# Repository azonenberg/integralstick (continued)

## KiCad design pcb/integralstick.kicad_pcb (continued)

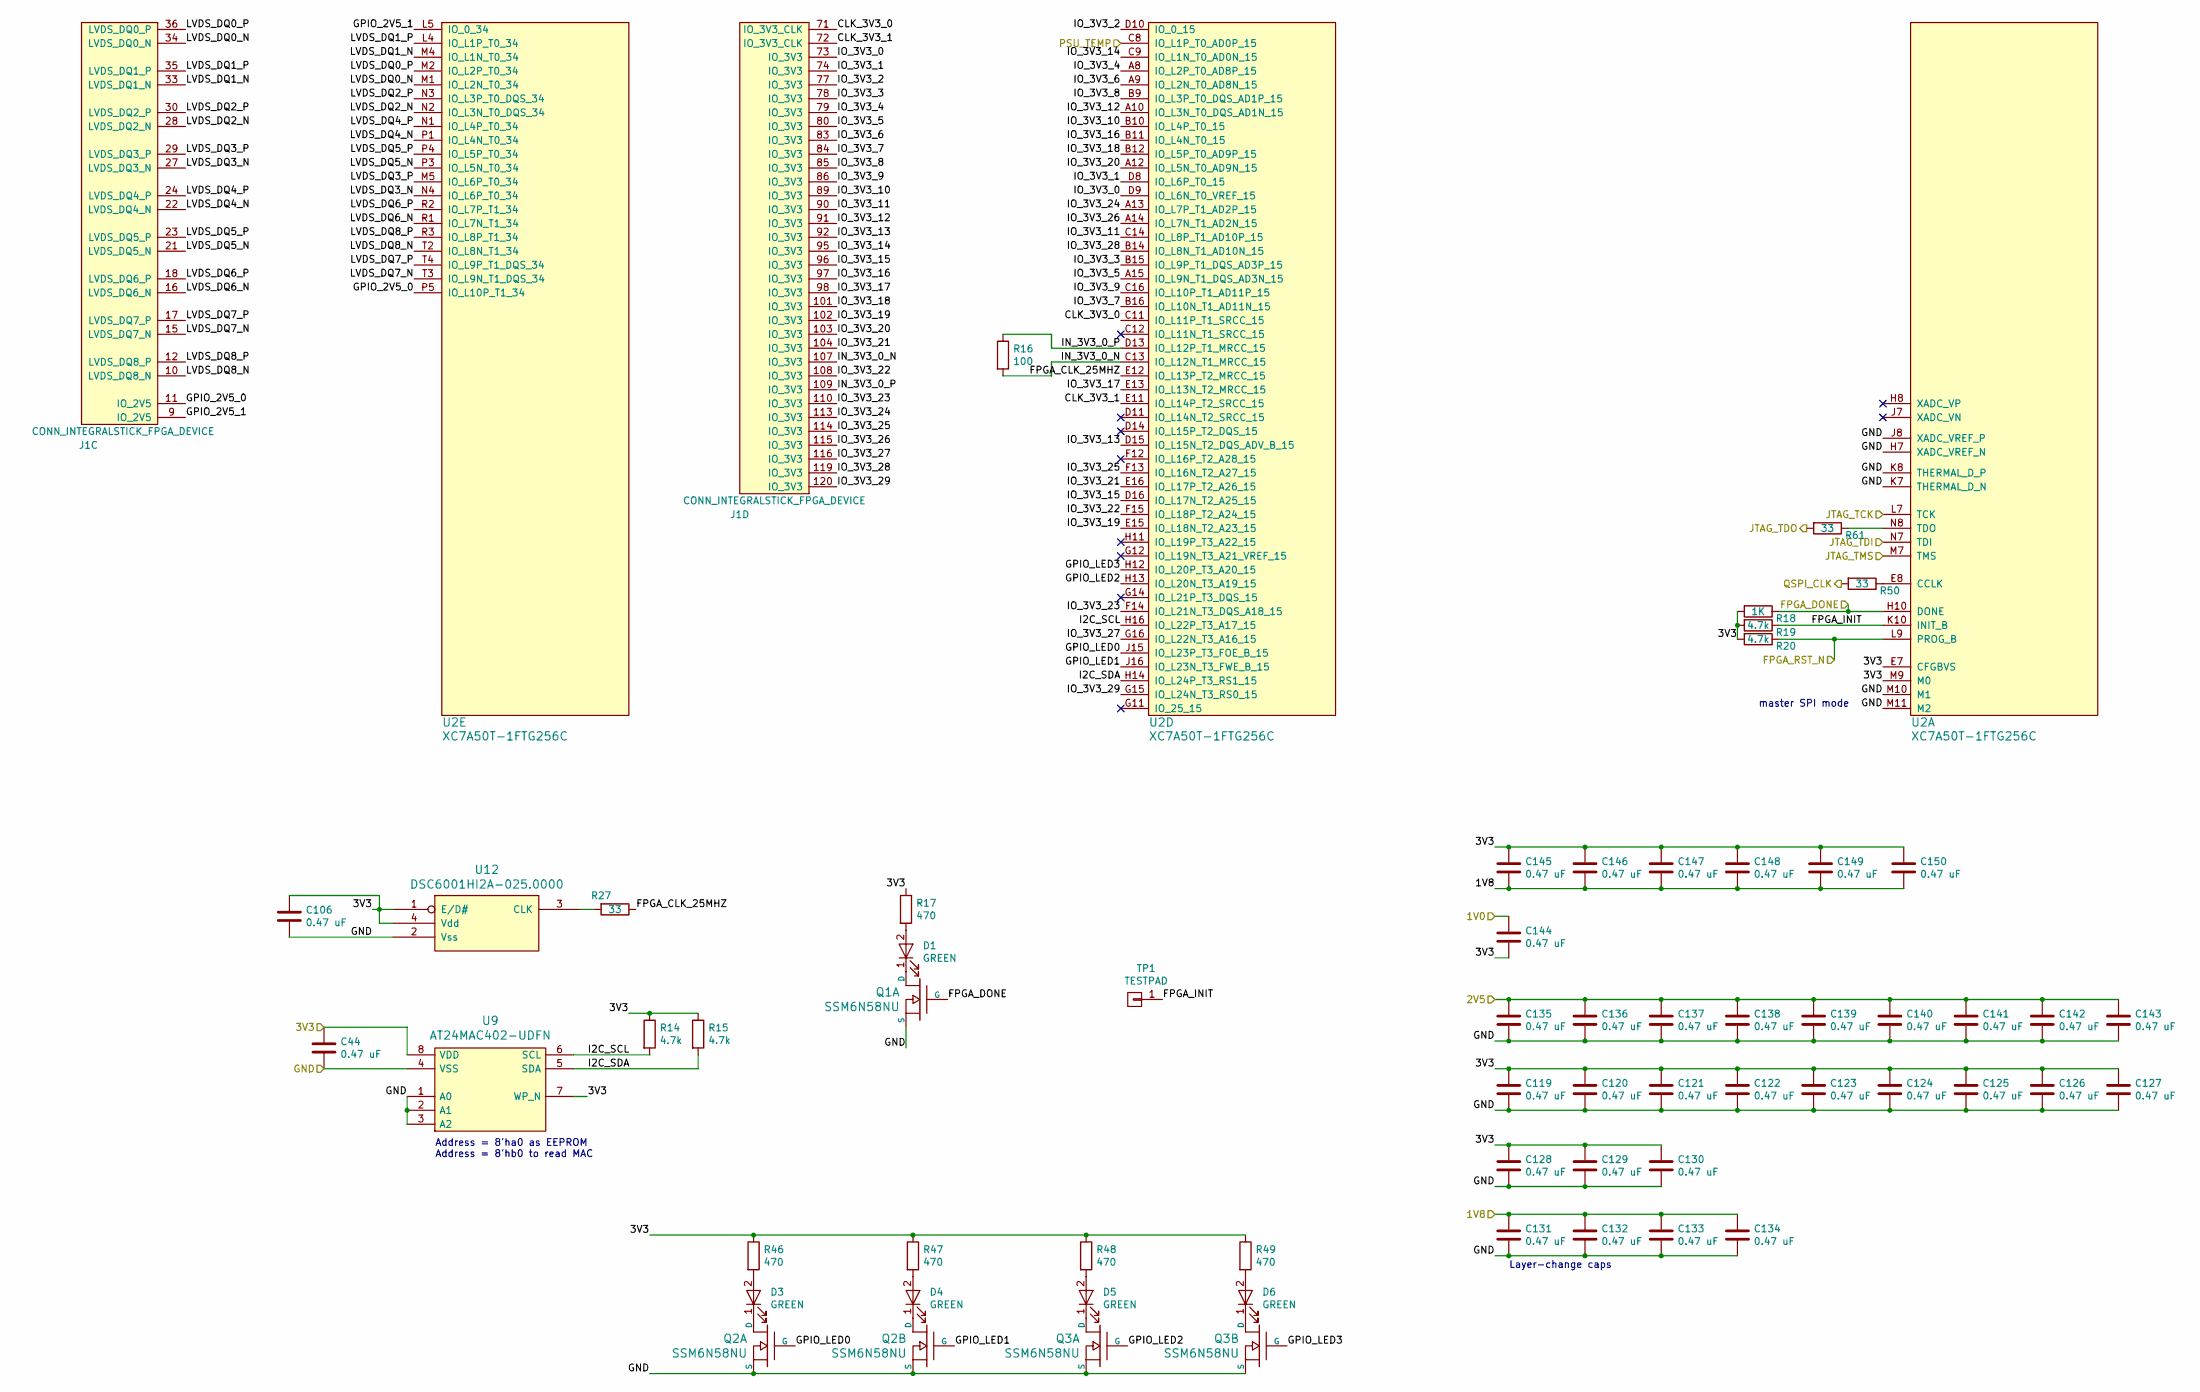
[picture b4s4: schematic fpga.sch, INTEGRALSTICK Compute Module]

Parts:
C44, C106, C119, C120, C121, C122, C123, C124, C125, C126, C127, C128, C129, C130, C131, C132, C133, C134, C135, C136, C137, C138, C139, C140, C141, C142, C143, C144, C145, C146, C147, C148, C149, C150: 0.47 uF; EIA_0402_CAP_NOSILK
D1, D3, D4, D5, D6: GREEN; EIA_0603_LED
J1: CONN_INTEGRALSTICK_FPGA_DEVICE; CONN_SAMTEC_QTH-060-01-L-D-A
Q1, Q2, Q3: SSM6N58NU; DFN_6_0.65MM_2x2MM_GDS
R14, R15, R19, R20: 4.7k; EIA_0402_RES_NOSILK
R16: 100; EIA_0402_RES_NOSILK
R17, R46, R47, R48, R49: 470; EIA_0402_RES_NOSILK
R18: 1K; EIA_0402_RES_NOSILK
R27, R50, R61: 33; EIA_0402_RES_NOSILK
TP1: TESTPAD; TESTPOINT_SMT_0.5MM
U2: XC7A50T-1FTG256C; BGA_256_17x17_FULLARRAY_1MM_0.4MM_FTG256
U9: AT24MAC402-UDFN; DFN_8_0.5MM_2x3MM
U12: DSC6001HI2A-025.0000‎; OSCILLATOR_1.6x1.2

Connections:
/1V0: C144.1; also elsewhere on the board
/1V8: C131.1, C132.1, C133.1, C134.1, C145.2, C146.2, C147.2, C148.2, C149.2, C150.2; also elsewhere on the board
/2V5: C135.1, C136.1, C137.1, C138.1, C139.1, C140.1, C141.1, C142.1, C143.1; also elsewhere on the board
/3V3: C44.1, C106.1, C119.1, C120.1, C121.1, C122.1, C123.1, C124.1, C125.1, C126.1, C127.1, C128.1, C129.1, C130.1, C144.2, C145.1, C146.1, C147.1, C148.1, C149.1, C150.1, R14.1, R15.1, R17.1, R18.2, R19.2, R20.2, R46.1, R47.1, R48.1, R49.1, U2.E7 (CFGBVS), U2.M9 (M0), U9.7 (WP_N), U9.8 (VDD), U12.1 (E/D#), U12.4 (Vdd); also elsewhere on the board
/FPGA/CLK_3V3_0: J1.71 (IO_3V3_CLK), U2.C11 (IO_L11P_T1_SRCC_15)
/FPGA/CLK_3V3_1: J1.72 (IO_3V3_CLK), U2.E11 (IO_L14P_T2_SRCC_15)
/FPGA/FPGA_CLK_25MHZ: R27.1, U2.E12 (IO_L13P_T2_MRCC_15)
/FPGA/FPGA_INIT: R19.1, TP1.1, U2.K10 (INIT_B)
/FPGA/GPIO_2V5_0: J1.11 (IO_2V5), U2.P5 (IO_L10P_T1_34)
/FPGA/GPIO_2V5_1: J1.9 (IO_2V5), U2.L5 (IO_0_34)
/FPGA/GPIO_LED0: Q2.G1 (G), U2.J15 (IO_L23P_T3_FOE_B_15)
/FPGA/GPIO_LED1: Q2.G2 (G), U2.J16 (IO_L23N_T3_FWE_B_15)
/FPGA/GPIO_LED2: Q3.G1 (G), U2.H13 (IO_L20N_T3_A19_15)
/FPGA/GPIO_LED3: Q3.G2 (G), U2.H12 (IO_L20P_T3_A20_15)
/FPGA/I2C_SCL: R14.2, U2.H16 (IO_L22P_T3_A17_15), U9.6 (SCL)
/FPGA/I2C_SDA: R15.2, U2.H14 (IO_L24P_T3_RS1_15), U9.5 (SDA)
/FPGA/IN_3V3_0_N: J1.107 (IO_3V3), R16.2, U2.C13 (IO_L12N_T1_MRCC_15)
/FPGA/IN_3V3_0_P: J1.109 (IO_3V3), R16.1, U2.D13 (IO_L12P_T1_MRCC_15)
/FPGA/IO_3V3_0: J1.73 (IO_3V3), U2.D9 (IO_L6N_T0_VREF_15)
/FPGA/IO_3V3_1: J1.74 (IO_3V3), U2.D8 (IO_L6P_T0_15)
/FPGA/IO_3V3_2: J1.77 (IO_3V3), U2.D10 (IO_0_15)
/FPGA/IO_3V3_3: J1.78 (IO_3V3), U2.B15 (IO_L9P_T1_DQS_AD3P_15)
/FPGA/IO_3V3_4: J1.79 (IO_3V3), U2.A8 (IO_L2P_T0_AD8P_15)
/FPGA/IO_3V3_5: J1.80 (IO_3V3), U2.A15 (IO_L9N_T1_DQS_AD3N_15)
/FPGA/IO_3V3_6: J1.83 (IO_3V3), U2.A9 (IO_L2N_T0_AD8N_15)
/FPGA/IO_3V3_7: J1.84 (IO_3V3), U2.B16 (IO_L10N_T1_AD11N_15)
/FPGA/IO_3V3_8: J1.85 (IO_3V3), U2.B9 (IO_L3P_T0_DQS_AD1P_15)
/FPGA/IO_3V3_9: J1.86 (IO_3V3), U2.C16 (IO_L10P_T1_AD11P_15)
/FPGA/IO_3V3_10: J1.89 (IO_3V3), U2.B10 (IO_L4P_T0_15)
/FPGA/IO_3V3_11: J1.90 (IO_3V3), U2.C14 (IO_L8P_T1_AD10P_15)
/FPGA/IO_3V3_12: J1.91 (IO_3V3), U2.A10 (IO_L3N_T0_DQS_AD1N_15)
/FPGA/IO_3V3_13: J1.92 (IO_3V3), U2.D15 (IO_L15N_T2_DQS_ADV_B_15)
/FPGA/IO_3V3_14: J1.95 (IO_3V3), U2.C9 (IO_L1N_T0_AD0N_15)
/FPGA/IO_3V3_15: J1.96 (IO_3V3), U2.D16 (IO_L17N_T2_A25_15)
/FPGA/IO_3V3_16: J1.97 (IO_3V3), U2.B11 (IO_L4N_T0_15)
/FPGA/IO_3V3_17: J1.98 (IO_3V3), U2.E13 (IO_L13N_T2_MRCC_15)
/FPGA/IO_3V3_18: J1.101 (IO_3V3), U2.B12 (IO_L5P_T0_AD9P_15)
/FPGA/IO_3V3_19: J1.102 (IO_3V3), U2.E15 (IO_L18N_T2_A23_15)
/FPGA/IO_3V3_20: J1.103 (IO_3V3), U2.A12 (IO_L5N_T0_AD9N_15)
/FPGA/IO_3V3_21: J1.104 (IO_3V3), U2.E16 (IO_L17P_T2_A26_15)
/FPGA/IO_3V3_22: J1.108 (IO_3V3), U2.F15 (IO_L18P_T2_A24_15)
/FPGA/IO_3V3_23: J1.110 (IO_3V3), U2.F14 (IO_L21N_T3_DQS_A18_15)
/FPGA/IO_3V3_24: J1.113 (IO_3V3), U2.A13 (IO_L7P_T1_AD2P_15)
/FPGA/IO_3V3_25: J1.114 (IO_3V3), U2.F13 (IO_L16N_T2_A27_15)
/FPGA/IO_3V3_26: J1.115 (IO_3V3), U2.A14 (IO_L7N_T1_AD2N_15)
/FPGA/IO_3V3_27: J1.116 (IO_3V3), U2.G16 (IO_L22N_T3_A16_15)
/FPGA/IO_3V3_28: J1.119 (IO_3V3), U2.B14 (IO_L8N_T1_AD10N_15)
/FPGA/IO_3V3_29: J1.120 (IO_3V3), U2.G15 (IO_L24N_T3_RS0_15)
/FPGA/LVDS_DQ0_N: J1.34 (LVDS_DQ0_N), U2.M1 (IO_L2N_T0_34)
/FPGA/LVDS_DQ0_P: J1.36 (LVDS_DQ0_P), U2.M2 (IO_L2P_T0_34)
/FPGA/LVDS_DQ1_N: J1.33 (LVDS_DQ1_N), U2.M4 (IO_L1N_T0_34)
/FPGA/LVDS_DQ1_P: J1.35 (LVDS_DQ1_P), U2.L4 (IO_L1P_T0_34)
/FPGA/LVDS_DQ2_N: J1.28 (LVDS_DQ2_N), U2.N2 (IO_L3N_T0_DQS_34)
/FPGA/LVDS_DQ2_P: J1.30 (LVDS_DQ2_P), U2.N3 (IO_L3P_T0_DQS_34)
/FPGA/LVDS_DQ3_N: J1.27 (LVDS_DQ3_N), U2.N4 (IO_L6P_T0_34)
/FPGA/LVDS_DQ3_P: J1.29 (LVDS_DQ3_P), U2.M5 (IO_L6P_T0_34)
/FPGA/LVDS_DQ4_N: J1.22 (LVDS_DQ4_N), U2.P1 (IO_L4N_T0_34)
/FPGA/LVDS_DQ4_P: J1.24 (LVDS_DQ4_P), U2.N1 (IO_L4P_T0_34)
/FPGA/LVDS_DQ5_N: J1.21 (LVDS_DQ5_N), U2.P3 (IO_L5N_T0_34)
/FPGA/LVDS_DQ5_P: J1.23 (LVDS_DQ5_P), U2.P4 (IO_L5P_T0_34)
/FPGA/LVDS_DQ6_N: J1.16 (LVDS_DQ6_N), U2.R1 (IO_L7N_T1_34)
/FPGA/LVDS_DQ6_P: J1.18 (LVDS_DQ6_P), U2.R2 (IO_L7P_T1_34)
/FPGA/LVDS_DQ7_N: J1.15 (LVDS_DQ7_N), U2.T3 (IO_L9N_T1_DQS_34)
/FPGA/LVDS_DQ7_P: J1.17 (LVDS_DQ7_P), U2.T4 (IO_L9P_T1_DQS_34)
/FPGA/LVDS_DQ8_N: J1.10 (LVDS_DQ8_N), U2.T2 (IO_L8N_T1_34)
/FPGA/LVDS_DQ8_P: J1.12 (LVDS_DQ8_P), U2.R3 (IO_L8P_T1_34)
/FPGA_DONE: Q1.G1 (G), R18.1, U2.H10 (DONE); also elsewhere on the board
/FPGA_RST_N: R20.1, U2.L9 (PROG_B); also elsewhere on the board
/FPGA_TDI: U2.N7 (TDI); also elsewhere on the board
/FPGA_TDO: R61.2; also elsewhere on the board
/GND: C44.2, C106.2, C119.2, C120.2, C121.2, C122.2, C123.2, C124.2, C125.2, C126.2, C127.2, C128.2, C129.2, C130.2, C131.2, C132.2, C133.2, C134.2, C135.2, C136.2, C137.2, C138.2, C139.2, C140.2, C141.2, C142.2, C143.2, Q1.S1 (S), Q2.S1 (S), Q2.S2 (S), Q3.S1 (S), Q3.S2 (S), U2.H7 (XADC_VREF_N), U2.J8 (XADC_VREF_P), U2.K7 (THERMAL_D_N), U2.K8 (THERMAL_D_P), U2.M10 (M1), U2.M11 (M2), U9.1 (A0), U9.2 (A1), U9.3 (A2), U9.4 (VSS), U12.2 (Vss); also elsewhere on the board
/JTAG_TCK: U2.L7 (TCK); also elsewhere on the board
/JTAG_TMS: U2.M7 (TMS); also elsewhere on the board
/PSU_TEMP: U2.C8 (IO_L1P_T0_AD0P_15); also elsewhere on the board
/QSPI_CLK: R50.2; also elsewhere on the board
unnamed: D1.1 (K), Q1.D1 (D)
unnamed: D1.2 (A), R17.2
unnamed: D3.1 (K), Q2.D1 (D)
unnamed: D3.2 (A), R46.2
unnamed: D4.1 (K), Q2.D2 (D)
unnamed: D4.2 (A), R47.2
unnamed: D5.1 (K), Q3.D1 (D)
unnamed: D5.2 (A), R48.2
unnamed: D6.1 (K), Q3.D2 (D)
unnamed: D6.2 (A), R49.2
unnamed: R27.2, U12.3 (CLK)
unnamed: R50.1, U2.E8 (CCLK)
unnamed: R61.1, U2.N8 (TDO)

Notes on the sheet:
Address = 8'ha0 as EEPROM Address = 8'hb0 to read MAC
master SPI mode
Layer-change caps

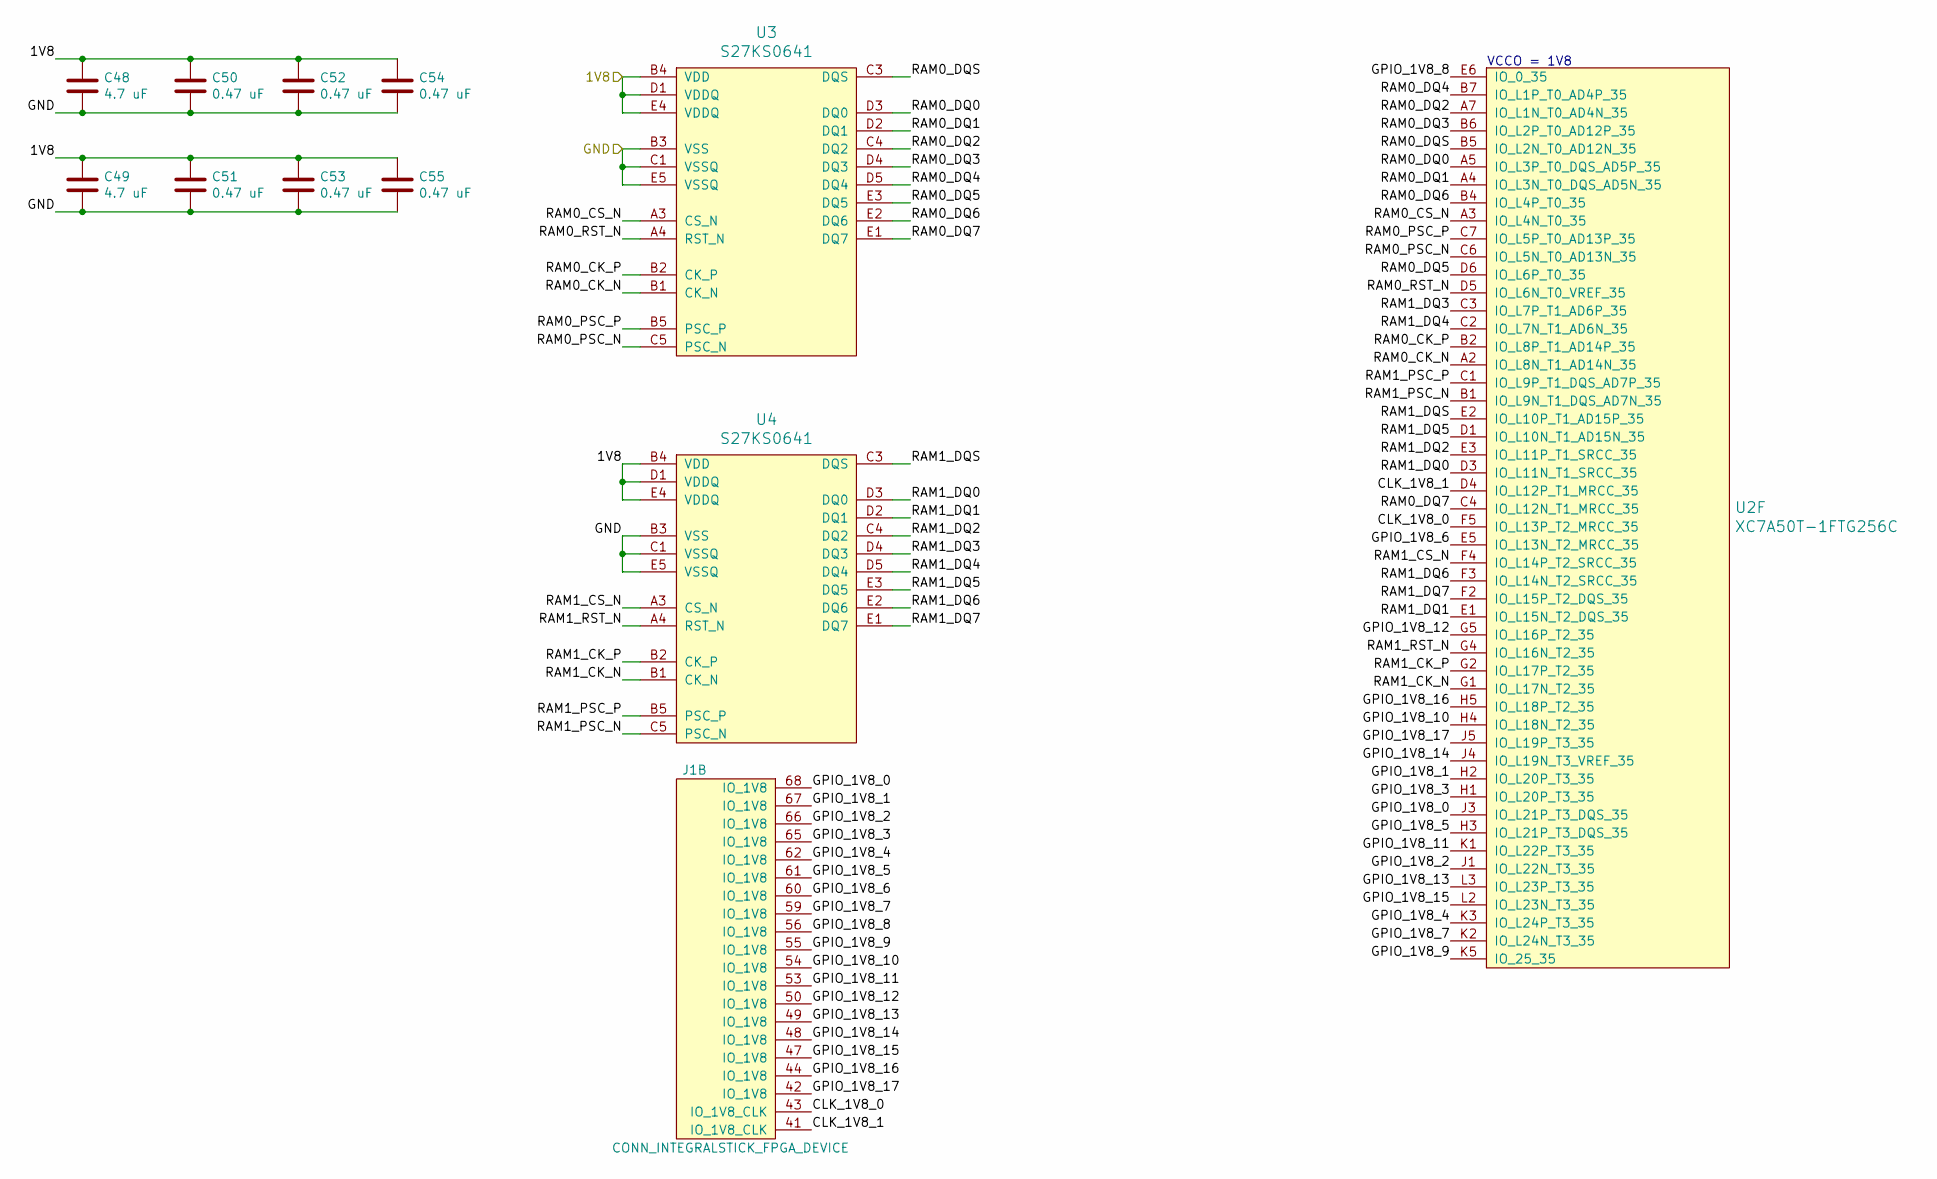
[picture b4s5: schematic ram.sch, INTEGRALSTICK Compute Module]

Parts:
C48, C49: 4.7 uF; EIA_0603_CAP_NOSILK
C50, C51, C52, C53, C54, C55: 0.47 uF; EIA_0402_CAP_NOSILK
J1: CONN_INTEGRALSTICK_FPGA_DEVICE; CONN_SAMTEC_QTH-060-01-L-D-A
U2: XC7A50T-1FTG256C; BGA_256_17x17_FULLARRAY_1MM_0.4MM_FTG256
U3, U4: S27KS0641; BGA_24_6x8_DEPOP1_1MM

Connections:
/1V8: C48.1, C49.1, C50.1, C51.1, C52.1, C53.1, C54.1, C55.1, U3.B4 (VDD), U3.D1 (VDDQ), U3.E4 (VDDQ), U4.B4 (VDD), U4.D1 (VDDQ), U4.E4 (VDDQ); also elsewhere on the board
/GND: C48.2, C49.2, C50.2, C51.2, C52.2, C53.2, C54.2, C55.2, U3.B3 (VSS), U3.C1 (VSSQ), U3.E5 (VSSQ), U4.B3 (VSS), U4.C1 (VSSQ), U4.E5 (VSSQ); also elsewhere on the board
/RAM/CLK_1V8_0: J1.43 (IO_1V8_CLK), U2.F5 (IO_L13P_T2_MRCC_35)
/RAM/CLK_1V8_1: J1.41 (IO_1V8_CLK), U2.D4 (IO_L12P_T1_MRCC_35)
/RAM/GPIO_1V8_0: J1.68 (IO_1V8), U2.J3 (IO_L21P_T3_DQS_35)
/RAM/GPIO_1V8_1: J1.67 (IO_1V8), U2.H2 (IO_L20P_T3_35)
/RAM/GPIO_1V8_2: J1.66 (IO_1V8), U2.J1 (IO_L22N_T3_35)
/RAM/GPIO_1V8_3: J1.65 (IO_1V8), U2.H1 (IO_L20P_T3_35)
/RAM/GPIO_1V8_4: J1.62 (IO_1V8), U2.K3 (IO_L24P_T3_35)
/RAM/GPIO_1V8_5: J1.61 (IO_1V8), U2.H3 (IO_L21P_T3_DQS_35)
/RAM/GPIO_1V8_6: J1.60 (IO_1V8), U2.E5 (IO_L13N_T2_MRCC_35)
/RAM/GPIO_1V8_7: J1.59 (IO_1V8), U2.K2 (IO_L24N_T3_35)
/RAM/GPIO_1V8_8: J1.56 (IO_1V8), U2.E6 (IO_0_35)
/RAM/GPIO_1V8_9: J1.55 (IO_1V8), U2.K5 (IO_25_35)
/RAM/GPIO_1V8_10: J1.54 (IO_1V8), U2.H4 (IO_L18N_T2_35)
/RAM/GPIO_1V8_11: J1.53 (IO_1V8), U2.K1 (IO_L22P_T3_35)
/RAM/GPIO_1V8_12: J1.50 (IO_1V8), U2.G5 (IO_L16P_T2_35)
/RAM/GPIO_1V8_13: J1.49 (IO_1V8), U2.L3 (IO_L23P_T3_35)
/RAM/GPIO_1V8_14: J1.48 (IO_1V8), U2.J4 (IO_L19N_T3_VREF_35)
/RAM/GPIO_1V8_15: J1.47 (IO_1V8), U2.L2 (IO_L23N_T3_35)
/RAM/GPIO_1V8_16: J1.44 (IO_1V8), U2.H5 (IO_L18P_T2_35)
/RAM/GPIO_1V8_17: J1.42 (IO_1V8), U2.J5 (IO_L19P_T3_35)
/RAM/RAM0_CK_N: U2.A2 (IO_L8N_T1_AD14N_35), U3.B1 (CK_N)
/RAM/RAM0_CK_P: U2.B2 (IO_L8P_T1_AD14P_35), U3.B2 (CK_P)
/RAM/RAM0_CS_N: U2.A3 (IO_L4N_T0_35), U3.A3 (CS_N)
/RAM/RAM0_DQ0: U2.A5 (IO_L3P_T0_DQS_AD5P_35), U3.D3 (DQ0)
/RAM/RAM0_DQ1: U2.A4 (IO_L3N_T0_DQS_AD5N_35), U3.D2 (DQ1)
/RAM/RAM0_DQ2: U2.A7 (IO_L1N_T0_AD4N_35), U3.C4 (DQ2)
/RAM/RAM0_DQ3: U2.B6 (IO_L2P_T0_AD12P_35), U3.D4 (DQ3)
/RAM/RAM0_DQ4: U2.B7 (IO_L1P_T0_AD4P_35), U3.D5 (DQ4)
/RAM/RAM0_DQ5: U2.D6 (IO_L6P_T0_35), U3.E3 (DQ5)
/RAM/RAM0_DQ6: U2.B4 (IO_L4P_T0_35), U3.E2 (DQ6)
/RAM/RAM0_DQ7: U2.C4 (IO_L12N_T1_MRCC_35), U3.E1 (DQ7)
/RAM/RAM0_DQS: U2.B5 (IO_L2N_T0_AD12N_35), U3.C3 (DQS)
/RAM/RAM0_PSC_N: U2.C6 (IO_L5N_T0_AD13N_35), U3.C5 (PSC_N)
/RAM/RAM0_PSC_P: U2.C7 (IO_L5P_T0_AD13P_35), U3.B5 (PSC_P)
/RAM/RAM0_RST_N: U2.D5 (IO_L6N_T0_VREF_35), U3.A4 (RST_N)
/RAM/RAM1_CK_N: U2.G1 (IO_L17N_T2_35), U4.B1 (CK_N)
/RAM/RAM1_CK_P: U2.G2 (IO_L17P_T2_35), U4.B2 (CK_P)
/RAM/RAM1_CS_N: U2.F4 (IO_L14P_T2_SRCC_35), U4.A3 (CS_N)
/RAM/RAM1_DQ0: U2.D3 (IO_L11N_T1_SRCC_35), U4.D3 (DQ0)
/RAM/RAM1_DQ1: U2.E1 (IO_L15N_T2_DQS_35), U4.D2 (DQ1)
/RAM/RAM1_DQ2: U2.E3 (IO_L11P_T1_SRCC_35), U4.C4 (DQ2)
/RAM/RAM1_DQ3: U2.C3 (IO_L7P_T1_AD6P_35), U4.D4 (DQ3)
/RAM/RAM1_DQ4: U2.C2 (IO_L7N_T1_AD6N_35), U4.D5 (DQ4)
/RAM/RAM1_DQ5: U2.D1 (IO_L10N_T1_AD15N_35), U4.E3 (DQ5)
/RAM/RAM1_DQ6: U2.F3 (IO_L14N_T2_SRCC_35), U4.E2 (DQ6)
/RAM/RAM1_DQ7: U2.F2 (IO_L15P_T2_DQS_35), U4.E1 (DQ7)
/RAM/RAM1_DQS: U2.E2 (IO_L10P_T1_AD15P_35), U4.C3 (DQS)
/RAM/RAM1_PSC_N: U2.B1 (IO_L9N_T1_DQS_AD7N_35), U4.C5 (PSC_N)
/RAM/RAM1_PSC_P: U2.C1 (IO_L9P_T1_DQS_AD7P_35), U4.B5 (PSC_P)
/RAM/RAM1_RST_N: U2.G4 (IO_L16N_T2_35), U4.A4 (RST_N)

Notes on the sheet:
VCCO = 1V8

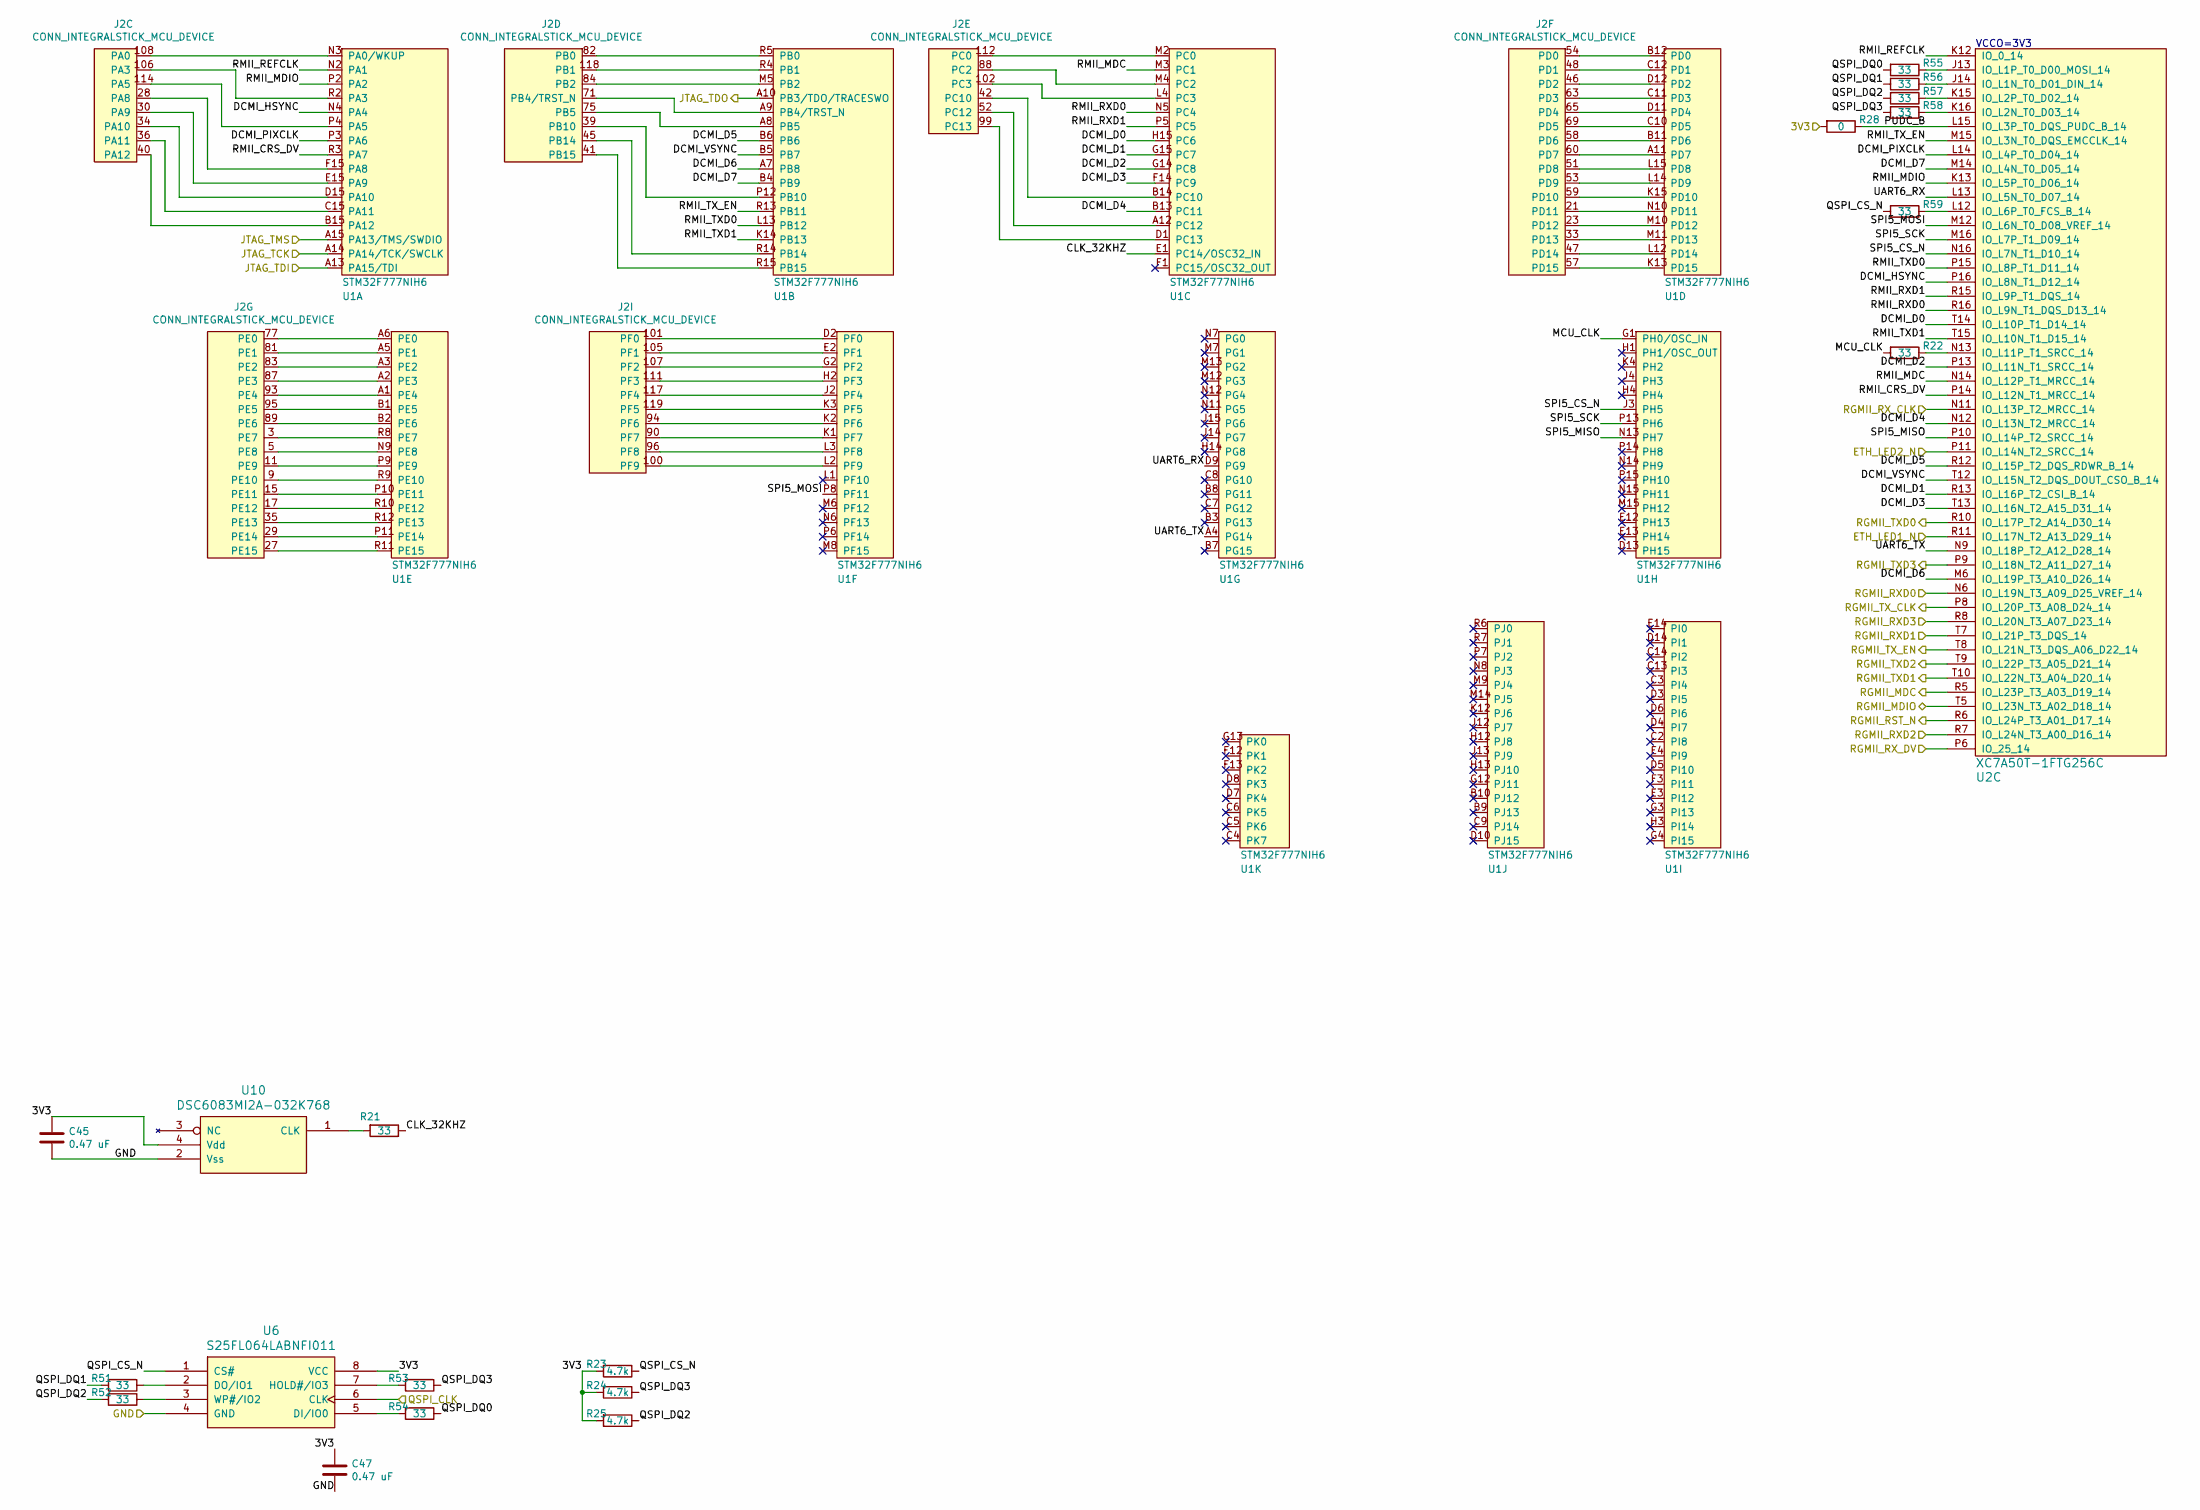
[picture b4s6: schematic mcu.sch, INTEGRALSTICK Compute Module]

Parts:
C45, C47: 0.47 uF; EIA_0402_CAP_NOSILK
J2: CONN_INTEGRALSTICK_MCU_DEVICE; CONN_SAMTEC_QTH-060-01-L-D-A
R21, R22, R51, R52, R53, R54, R55, R56, R57, R58, R59: 33; EIA_0402_RES_NOSILK
R23, R24, R25: 4.7k; EIA_0402_RES_NOSILK
R28: 0; EIA_0402_CAP_NOSILK
U1: STM32F777NIH6‎; BGA_216_13x13_DEPOP3x3_0.8MM
U2: XC7A50T-1FTG256C; BGA_256_17x17_FULLARRAY_1MM_0.4MM_FTG256
U6: S25FL064LABNFI011‎; DFN_8_1.27MM_6x5MM
U10: DSC6083MI2A-032K768; OSCILLATOR_2.0x1.6

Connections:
/3V3: C45.1, C47.1, R23.2, R24.2, R25.2, R28.2, U6.8 (VCC), U10.4 (Vdd); also elsewhere on the board
/ETH_LED1_N: U2.R11 (IO_L17N_T2_A13_D29_14); also elsewhere on the board
/ETH_LED2_N: U2.P11 (IO_L14N_T2_SRCC_14); also elsewhere on the board
/Ethernet/RGMII_MDC: U2.R5 (IO_L23P_T3_A03_D19_14); also elsewhere on the board
/Ethernet/RGMII_MDIO: U2.T5 (IO_L23N_T3_A02_D18_14); also elsewhere on the board
/Ethernet/RGMII_RST_N: U2.R6 (IO_L24P_T3_A01_D17_14); also elsewhere on the board
/Ethernet/RGMII_RXD0: U2.N6 (IO_L19N_T3_A09_D25_VREF_14); also elsewhere on the board
/Ethernet/RGMII_RXD1: U2.T7 (IO_L21P_T3_DQS_14); also elsewhere on the board
/Ethernet/RGMII_RXD2: U2.R7 (IO_L24N_T3_A00_D16_14); also elsewhere on the board
/Ethernet/RGMII_RXD3: U2.R8 (IO_L20N_T3_A07_D23_14); also elsewhere on the board
/Ethernet/RGMII_RX_CLK: U2.N11 (IO_L13P_T2_MRCC_14); also elsewhere on the board
/Ethernet/RGMII_RX_DV: U2.P6 (IO_25_14); also elsewhere on the board
/Ethernet/RGMII_TXD0: U2.R10 (IO_L17P_T2_A14_D30_14); also elsewhere on the board
/Ethernet/RGMII_TXD1: U2.T10 (IO_L22N_T3_A04_D20_14); also elsewhere on the board
/Ethernet/RGMII_TXD2: U2.T9 (IO_L22P_T3_A05_D21_14); also elsewhere on the board
/Ethernet/RGMII_TXD3: U2.P9 (IO_L18N_T2_A11_D27_14); also elsewhere on the board
/Ethernet/RGMII_TX_CLK: U2.P8 (IO_L20P_T3_A08_D24_14); also elsewhere on the board
/Ethernet/RGMII_TX_EN: U2.T8 (IO_L21N_T3_DQS_A06_D22_14); also elsewhere on the board
/FPGA_TDO: U1.A13 (PA15/TDI); also elsewhere on the board
/GND: C45.2, C47.2, U6.4 (GND), U10.2 (Vss); also elsewhere on the board
/JTAG_TCK: U1.A14 (PA14/TCK/SWCLK); also elsewhere on the board
/JTAG_TMS: U1.A15 (PA13/TMS/SWDIO); also elsewhere on the board
/MCU/CLK_32KHZ: R21.1, U1.E1 (PC14/OSC32_IN)
/MCU/DCMI_D0: U1.H15 (PC6), U2.T14 (IO_L10P_T1_D14_14)
/MCU/DCMI_D1: U1.G15 (PC7), U2.R13 (IO_L16P_T2_CSI_B_14)
/MCU/DCMI_D2: U1.G14 (PC8), U2.P13 (IO_L11N_T1_SRCC_14)
/MCU/DCMI_D3: U1.F14 (PC9), U2.T13 (IO_L16N_T2_A15_D31_14)
/MCU/DCMI_D4: U1.B13 (PC11), U2.N12 (IO_L13N_T2_MRCC_14)
/MCU/DCMI_D5: U1.B6, U2.R12 (IO_L15P_T2_DQS_RDWR_B_14)
/MCU/DCMI_D6: U1.A7 (PB8), U2.M6 (IO_L19P_T3_A10_D26_14)
/MCU/DCMI_D7: U1.B4 (PB9), U2.M14 (IO_L4N_T0_D05_14)
/MCU/DCMI_HSYNC: U1.N4 (PA4), U2.P16 (IO_L8N_T1_D12_14)
/MCU/DCMI_PIXCLK: U1.P3 (PA6), U2.L14 (IO_L4P_T0_D04_14)
/MCU/DCMI_VSYNC: U1.B5 (PB7), U2.T12 (IO_L15N_T2_DQS_DOUT_CSO_B_14)
/MCU/JTAG_TDO: U1.A10 (PB3/TDO/TRACESWO); also elsewhere on the board
/MCU/MCU_CLK: R22.2, U1.G1 (PH0/OSC_IN)
/MCU/PUDC_B: R28.1, U2.L15 (IO_L3P_T0_DQS_PUDC_B_14)
/MCU/QSPI_CS_N: R23.1, R59.2, U6.1 (CS#)
/MCU/QSPI_DQ0: R54.1, R55.2
/MCU/QSPI_DQ1: R51.2, R56.2
/MCU/QSPI_DQ2: R25.1, R52.2, R57.2
/MCU/QSPI_DQ3: R24.1, R53.1, R58.2
/MCU/RMII_CRS_DV: U1.R3 (PA7), U2.P14 (IO_L12N_T1_MRCC_14)
/MCU/RMII_MDC: U1.M3 (PC1), U2.N14 (IO_L12P_T1_MRCC_14)
/MCU/RMII_MDIO: U1.P2 (PA2), U2.K13 (IO_L5P_T0_D06_14)
/MCU/RMII_REFCLK: U1.N2 (PA1), U2.K12 (IO_0_14)
/MCU/RMII_RXD0: U1.N5 (PC4), U2.R16 (IO_L9N_T1_DQS_D13_14)
/MCU/RMII_RXD1: U1.P5 (PC5), U2.R15 (IO_L9P_T1_DQS_14)
/MCU/RMII_TXD0: U1.L13 (PB12), U2.P15 (IO_L8P_T1_D11_14)
/MCU/RMII_TXD1: U1.K14 (PB13), U2.T15 (IO_L10N_T1_D15_14)
/MCU/RMII_TX_EN: U1.R13 (PB11), U2.M15 (IO_L3N_T0_DQS_EMCCLK_14)
/MCU/SPI5_CS_N: U1.J3 (PH5), U2.N16 (IO_L7N_T1_D10_14)
/MCU/SPI5_MISO: U1.N13 (PH7), U2.P10 (IO_L14P_T2_SRCC_14)
/MCU/SPI5_MOSI: U1.P8 (PF11), U2.M12 (IO_L6N_T0_D08_VREF_14)
/MCU/SPI5_SCK: U1.P13 (PH6), U2.M16 (IO_L7P_T1_D09_14)
/MCU/UART6_RX: U1.D9 (PG9), U2.L13 (IO_L5N_T0_D07_14)
/MCU/UART6_TX: U1.A4 (PG14), U2.N9 (IO_L18P_T2_A12_D28_14)
/QSPI_CLK: U6.6 (CLK); also elsewhere on the board
unnamed: J2.3 (PE7), U1.R8 (PE7)
unnamed: J2.5 (PE8), U1.N9 (PE8)
unnamed: J2.9 (PE10), U1.R9 (PE10)
unnamed: J2.11 (PE9), U1.P9 (PE9)
unnamed: J2.15 (PE11), U1.P10 (PE11)
unnamed: J2.17 (PE12), U1.R10 (PE12)
unnamed: J2.21 (PD11), U1.N10 (PD11)
unnamed: J2.23 (PD12), U1.M10 (PD12)
unnamed: J2.27 (PE15), U1.R11 (PE15)
unnamed: J2.28 (PA8), U1.F15 (PA8)
unnamed: J2.29 (PE14), U1.P11 (PE14)
unnamed: J2.30 (PA9), U1.E15 (PA9)
unnamed: J2.33 (PD13), U1.M11 (PD13)
unnamed: J2.34 (PA10), U1.D15 (PA10)
unnamed: J2.35 (PE13), U1.R12 (PE13)
unnamed: J2.36 (PA11), U1.C15 (PA11)
unnamed: J2.39 (PB10), U1.P12 (PB10)
unnamed: J2.40 (PA12), U1.B15 (PA12)
unnamed: J2.41 (PB15), U1.R15 (PB15)
unnamed: J2.42 (PC10), U1.B14 (PC10)
unnamed: J2.45 (PB14), U1.R14 (PB14)
unnamed: J2.46 (PD2), U1.D12 (PD2)
unnamed: J2.47 (PD14), U1.L12 (PD14)
unnamed: J2.48 (PD1), U1.C12 (PD1)
unnamed: J2.51 (PD8), U1.L15 (PD8)
unnamed: J2.52 (PC12), U1.A12 (PC12)
unnamed: J2.53 (PD9), U1.L14 (PD9)
unnamed: J2.54 (PD0), U1.B12 (PD0)
unnamed: J2.57 (PD15), U1.K13 (PD15)
unnamed: J2.58 (PD6), U1.B11 (PD6)
unnamed: J2.59 (PD10), U1.K15 (PD10)
unnamed: J2.60 (PD7), U1.A11 (PD7)
unnamed: J2.63 (PD3), U1.C11 (PD3)
unnamed: J2.65 (PD4), U1.D11 (PD4)
unnamed: J2.69 (PD5), U1.C10 (PD5)
unnamed: J2.71 (PB4/TRST_N), U1.A9 (PB4/TRST_N)
unnamed: J2.75 (PB5), U1.A8 (PB5)
unnamed: J2.77 (PE0), U1.A6 (PE0)
unnamed: J2.81 (PE1), U1.A5 (PE1)
unnamed: J2.82 (PB0), U1.R5 (PB0)
unnamed: J2.83 (PE2), U1.A3 (PE2)
unnamed: J2.84 (PB2), U1.M5 (PB2)
unnamed: J2.87 (PE3), U1.A2 (PE3)
unnamed: J2.88 (PC2), U1.M4 (PC2)
unnamed: J2.89 (PE6), U1.B2 (PE6)
unnamed: J2.90 (PF7), U1.K1 (PF7)
unnamed: J2.93 (PE4), U1.A1 (PE4)
unnamed: J2.94 (PF6), U1.K2 (PF6)
unnamed: J2.95 (PE5), U1.B1 (PE5)
unnamed: J2.96 (PF8), U1.L3 (PF8)
unnamed: J2.99 (PC13), U1.D1 (PC13)
unnamed: J2.100 (PF9), U1.L2 (PF9)
unnamed: J2.101 (PF0), U1.D2 (PF0)
unnamed: J2.102 (PC3), U1.L4 (PC3)
unnamed: J2.105 (PF1), U1.E2 (PF1)
unnamed: J2.106 (PA3), U1.R2 (PA3)
unnamed: J2.107 (PF2), U1.G2 (PF2)
unnamed: J2.108 (PA0), U1.N3 (PA0/WKUP)
unnamed: J2.111 (PF3), U1.H2 (PF3)
unnamed: J2.112 (PC0), U1.M2 (PC0)
unnamed: J2.114 (PA5), U1.P4 (PA5)
unnamed: J2.117 (PF4), U1.J2 (PF4)
unnamed: J2.118 (PB1), U1.R4 (PB1)
unnamed: J2.119 (PF5), U1.K3 (PF5)
unnamed: R21.2, U10.1 (CLK)
unnamed: R22.1, U2.N13 (IO_L11P_T1_SRCC_14)
unnamed: R51.1, U6.2 (DO/IO1)
unnamed: R52.1, U6.3 (WP#/IO2)
unnamed: R53.2, U6.7 (HOLD#/IO3)
unnamed: R54.2, U6.5 (DI/IO0)
unnamed: R55.1, U2.J13 (IO_L1P_T0_D00_MOSI_14)
unnamed: R56.1, U2.J14 (IO_L1N_T0_D01_DIN_14)
unnamed: R57.1, U2.K15 (IO_L2P_T0_D02_14)
unnamed: R58.1, U2.K16 (IO_L2N_T0_D03_14)
unnamed: R59.1, U2.L12 (IO_L6P_T0_FCS_B_14)

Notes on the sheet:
VCCO=3V3

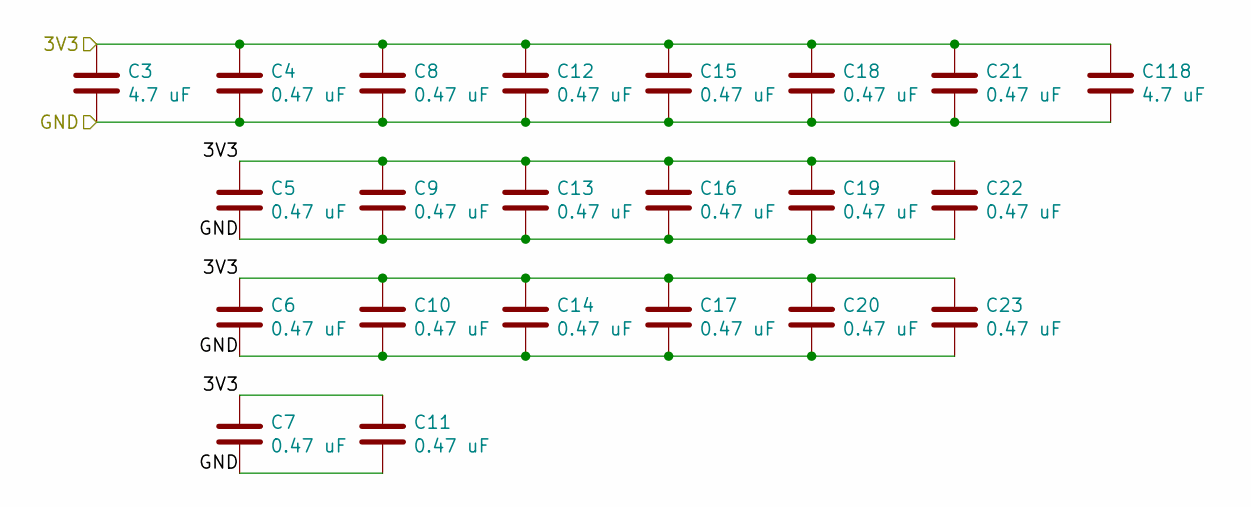
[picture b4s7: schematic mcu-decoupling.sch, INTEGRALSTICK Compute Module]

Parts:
C3, C118: 4.7 uF; EIA_0603_CAP_NOSILK
C4, C5, C6, C7, C8, C9, C10, C11, C12, C13, C14, C15, C16, C17, C18, C19, C20, C21, C22, C23: 0.47 uF; EIA_0402_CAP_NOSILK

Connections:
/3V3: C3.1, C4.1, C5.1, C6.1, C7.1, C8.1, C9.1, C10.1, C11.1, C12.1, C13.1, C14.1, C15.1, C16.1, C17.1, C18.1, C19.1, C20.1, C21.1, C22.1, C23.1, C118.1; also elsewhere on the board
/GND: C3.2, C4.2, C5.2, C6.2, C7.2, C8.2, C9.2, C10.2, C11.2, C12.2, C13.2, C14.2, C15.2, C16.2, C17.2, C18.2, C19.2, C20.2, C21.2, C22.2, C23.2, C118.2; also elsewhere on the board

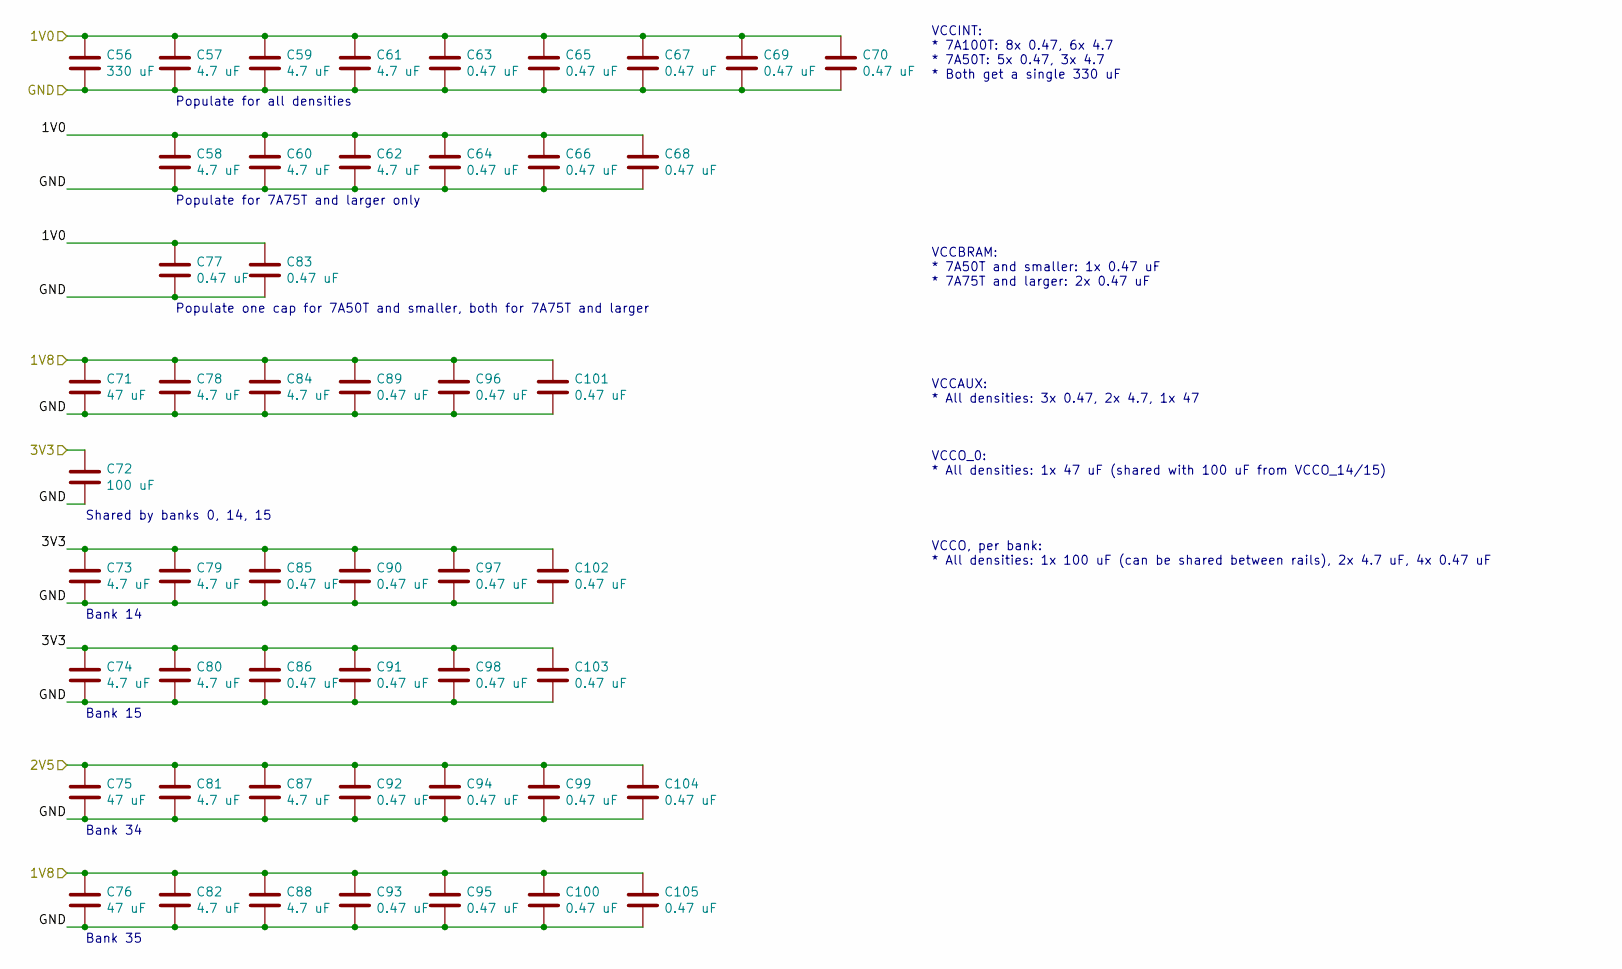
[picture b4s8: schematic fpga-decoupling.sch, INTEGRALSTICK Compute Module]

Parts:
C56: 330 uF; EIA_1210_CAP_NOSILK
C57, C58, C59, C60, C61, C62, C73, C74, C78, C79, C80, C81, C82, C84, C87, C88: 4.7 uF; EIA_0603_CAP_NOSILK
C63, C64, C65, C66, C67, C68, C69, C70, C77, C83, C85, C86, C89, C90, C91, C92, C93, C94, C95, C96, C97, C98, C99, C100, C101, C102, C103, C104, C105: 0.47 uF; EIA_0402_CAP_NOSILK
C71, C75, C76: 47 uF; EIA_1206_CAP_NOSILK
C72: 100 uF; EIA_1206_CAP_NOSILK

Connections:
/1V0: C56.1, C57.1, C58.1, C59.1, C60.1, C61.1, C62.1, C63.1, C64.1, C65.1, C66.1, C67.1, C68.1, C69.1, C70.1, C77.1, C83.1; also elsewhere on the board
/1V8: C71.1, C76.1, C78.1, C82.1, C84.1, C88.1, C89.1, C93.1, C95.1, C96.1, C100.1, C101.1, C105.1; also elsewhere on the board
/2V5: C75.1, C81.1, C87.1, C92.1, C94.1, C99.1, C104.1; also elsewhere on the board
/3V3: C72.1, C73.1, C74.1, C79.1, C80.1, C85.1, C86.1, C90.1, C91.1, C97.1, C98.1, C102.1, C103.1; also elsewhere on the board
/GND: C56.2, C57.2, C58.2, C59.2, C60.2, C61.2, C62.2, C63.2, C64.2, C65.2, C66.2, C67.2, C68.2, C69.2, C70.2, C71.2, C72.2, C73.2, C74.2, C75.2, C76.2, C77.2, C78.2, C79.2, C80.2, C81.2, C82.2, C83.2, C84.2, C85.2, C86.2, C87.2, C88.2, C89.2, C90.2, C91.2, C92.2, C93.2, C94.2, C95.2, C96.2, C97.2, C98.2, C99.2, C100.2, C101.2, C102.2, C103.2, C104.2, C105.2; also elsewhere on the board

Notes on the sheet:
VCCINT: * 7A100T: 8x 0.47, 6x 4.7 * 7A50T: 5x 0.47, 3x 4.7 * Both get a single 330 uF
Populate for 7A75T and larger only
Populate for all densities
VCCBRAM: * 7A50T and smaller: 1x 0.47 uF * 7A75T and larger: 2x 0.47 uF
Populate one cap for 7A50T and smaller, both for 7A75T and larger
VCCAUX: * All densities: 3x 0.47, 2x 4.7, 1x 47
VCCO_0: * All densities: 1x 47 uF (shared with 100 uF from VCCO_14/15)
VCCO, per bank: * All densities: 1x 100 uF (can be shared between rails), 2x 4.7 uF, 4x 0.47 uF
Shared by banks 0, 14, 15
Bank 14
Bank 15
Bank 34
Bank 35
